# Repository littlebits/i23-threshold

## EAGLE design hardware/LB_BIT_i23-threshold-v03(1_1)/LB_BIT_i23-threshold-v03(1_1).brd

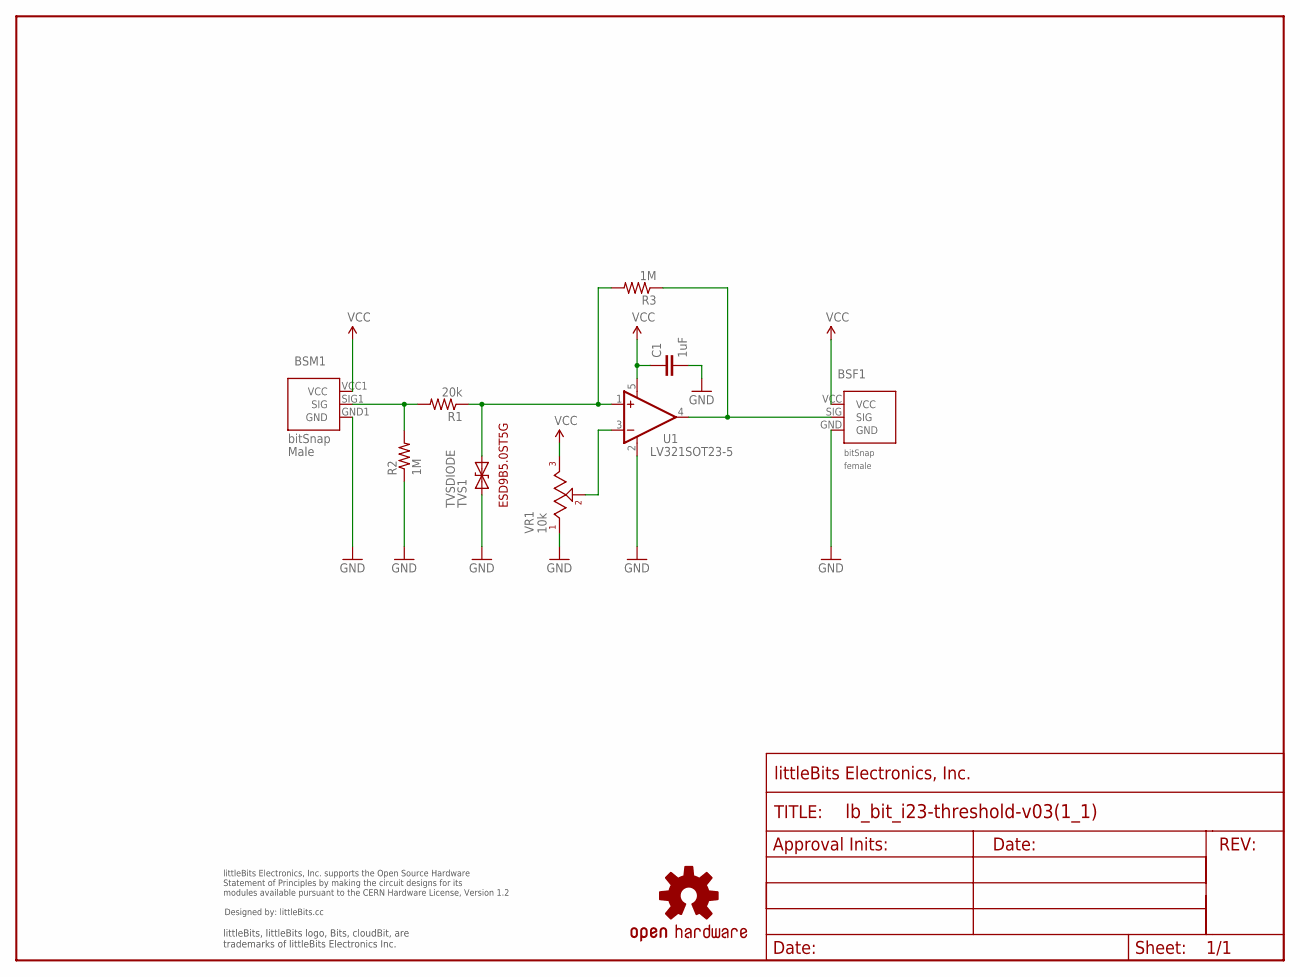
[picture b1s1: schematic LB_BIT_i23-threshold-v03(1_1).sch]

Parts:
BSF1: BITSNAP_V03_FEMALE
BSM1: BITSNAP_V03_MALE
C1: 1uF; CAP-0603
R1: 20k; RES-0603
R2, R3: 1M; RES-0603
TVS1: TVSDIODE; SOD-923
U1: LV321SOT23-5; SOT23-5
U$3: OSHW-LOGOL; OSHW-LOGO-L
U$5: FRAME-LETTER-OHWOHW; FABDWG01-OHW
U$31: OSHWCREDIT
VR1: 10k; 9MM_POT

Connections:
GND: BSF1.GND, BSM1.GND1 (GND), C1.2, R2.1, TVS1.1 (A), U1.2 (V-), VR1.1
unnamed: BSM1.SIG1 (SIG), R1.2, R2.2
unnamed: U1.3 (-IN), VR1.2
unnamed: R1.1, R3.2, TVS1.2 (C), U1.1 (+IN)
unnamed: BSF1.SIG, R3.1, U1.4 (OUT)
VCC: BSF1.VCC, BSM1.VCC1 (VCC), C1.1, U1.5 (V+), VR1.3

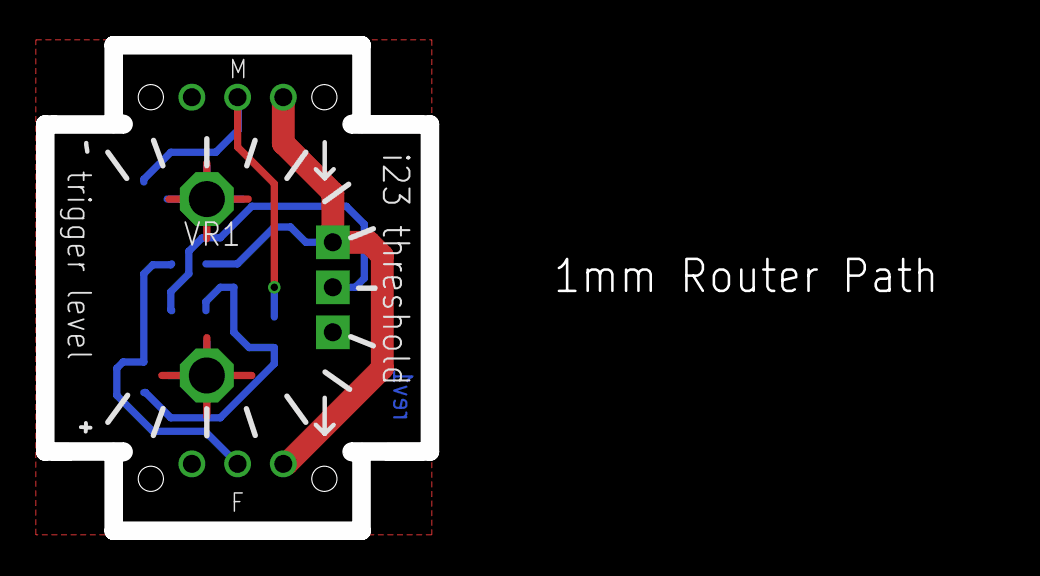
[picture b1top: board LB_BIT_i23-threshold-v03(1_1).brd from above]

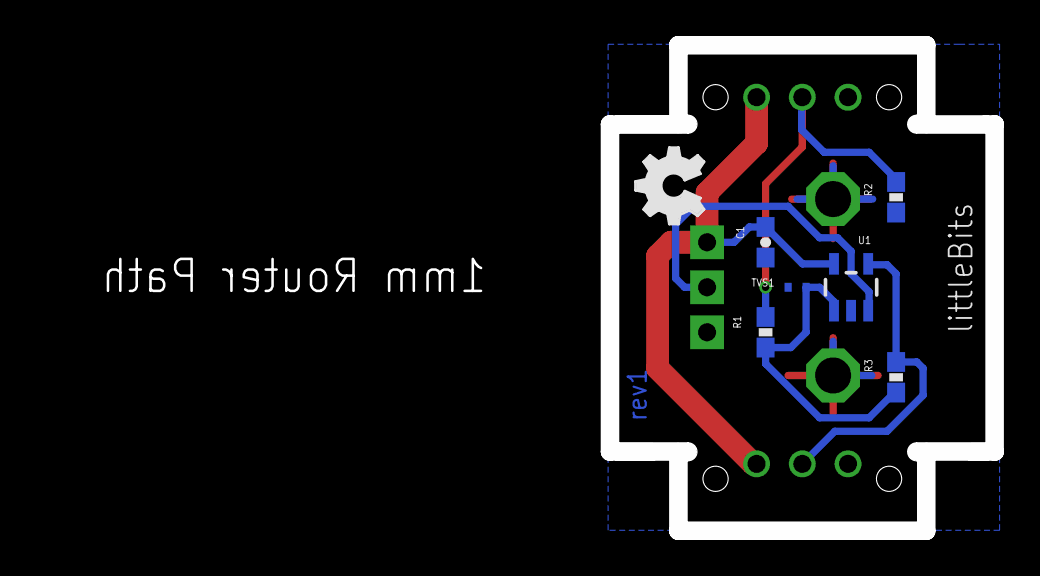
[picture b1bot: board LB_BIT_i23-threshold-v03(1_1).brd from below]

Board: 2 copper layers, 52.8 x 27.0 mm, 15 parts (7 on the bottom side), 6 nets.

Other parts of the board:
U$2: OSHW_FILLX150_NOTEXT
U$29: +
U$30: -

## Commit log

2014-11-18 First commit, added hardware files

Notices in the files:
parts and their libraries:
LITTLEBITS: modules available pursuant to the CERN Hardware License,
Version 1.2
LITTLEBITS: modules available pursuant to the CERN Hardware License, Version 1.2
